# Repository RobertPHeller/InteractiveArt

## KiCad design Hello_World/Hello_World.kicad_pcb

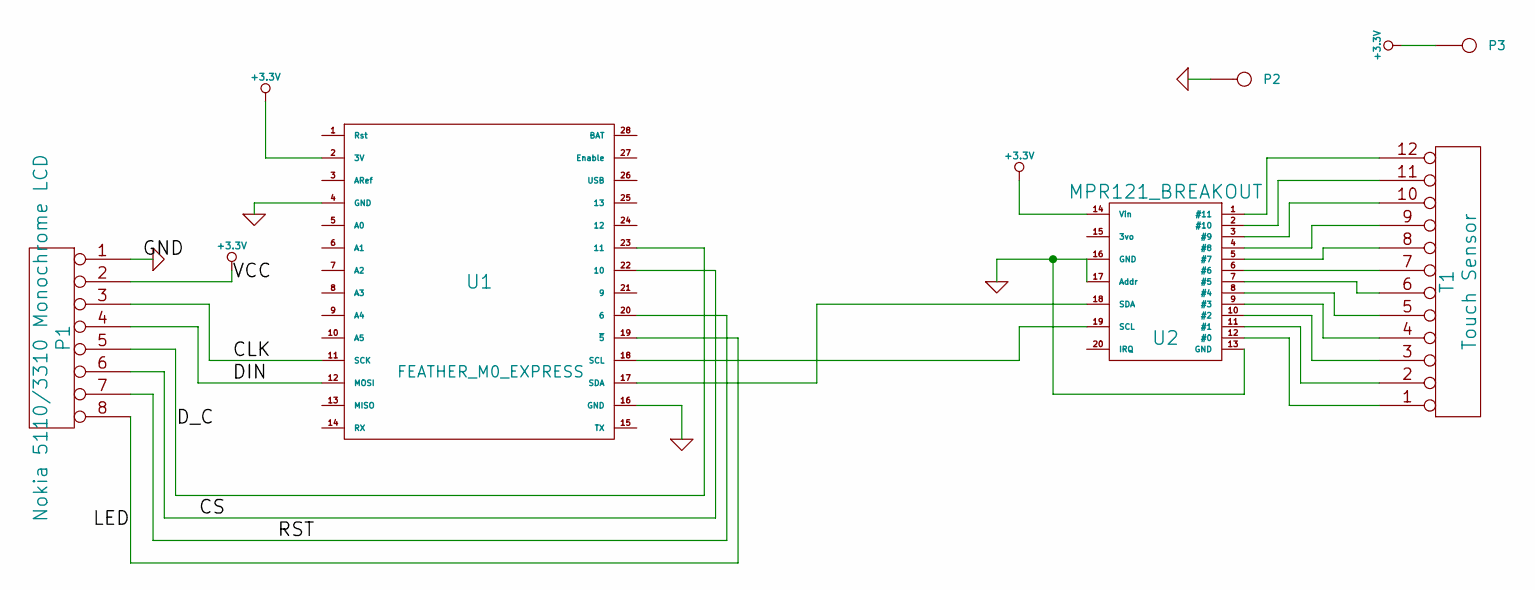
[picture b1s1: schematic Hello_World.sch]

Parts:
P1: Nokia 5110/3310 Monochrome LCD
P2, P3: CONN_1
T1: Touch Sensor
U1: FEATHER_M0_EXPRESS
U2: MPR121_BREAKOUT

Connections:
+3.3V: P1.2, P3.1, U1.2 (3V), U2.14 (Vin)
/CLK: P1.3, U1.11 (SCK)
/CS: P1.6, U1.22 (10~)
/DIN: P1.4, U1.12 (MOSI)
/D_C: P1.5, U1.23 (11~)
/LED: P1.8, U1.19 (~5)
/RST: P1.7, U1.20 (6)
GND: P1.1, P2.1, U1.4 (GND), U1.16 (GND), U2.13 (GND), U2.16 (GND), U2.17 (Addr)
unnamed: T1.4, U2.9 (#3)
unnamed: T1.3, U2.10 (#2)
unnamed: T1.2, U2.11 (#1)
unnamed: T1.1, U2.12 (#0)
unnamed: T1.12, U2.1 (#11)
unnamed: T1.11, U2.2 (#10)
unnamed: T1.10, U2.3 (#9)
unnamed: T1.9, U2.4 (#8)
unnamed: T1.8, U2.5 (#7)
unnamed: T1.7, U2.6 (#6)
unnamed: T1.6, U2.7 (#5)
unnamed: T1.5, U2.8 (#4)
unnamed: U1.17 (SDA), U2.18 (SDA)
unnamed: U1.18 (SCL), U2.19 (SCL)

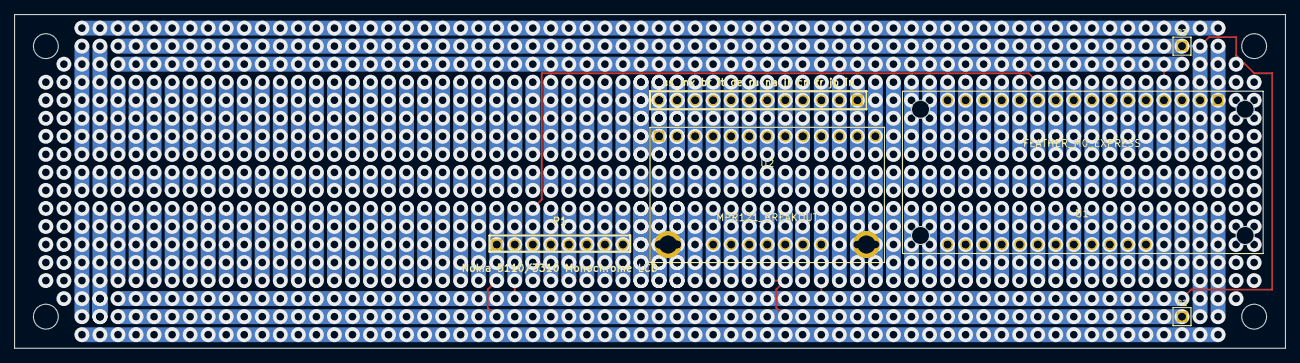
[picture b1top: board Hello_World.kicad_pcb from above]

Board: 8 copper layers, 179.0 x 47.0 mm, 6 parts (0 on the bottom side), 22 nets.
